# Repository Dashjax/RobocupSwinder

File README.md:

# RobocupSwinder
Robocup intro project with the goal to create a solenoid coil winder. :)

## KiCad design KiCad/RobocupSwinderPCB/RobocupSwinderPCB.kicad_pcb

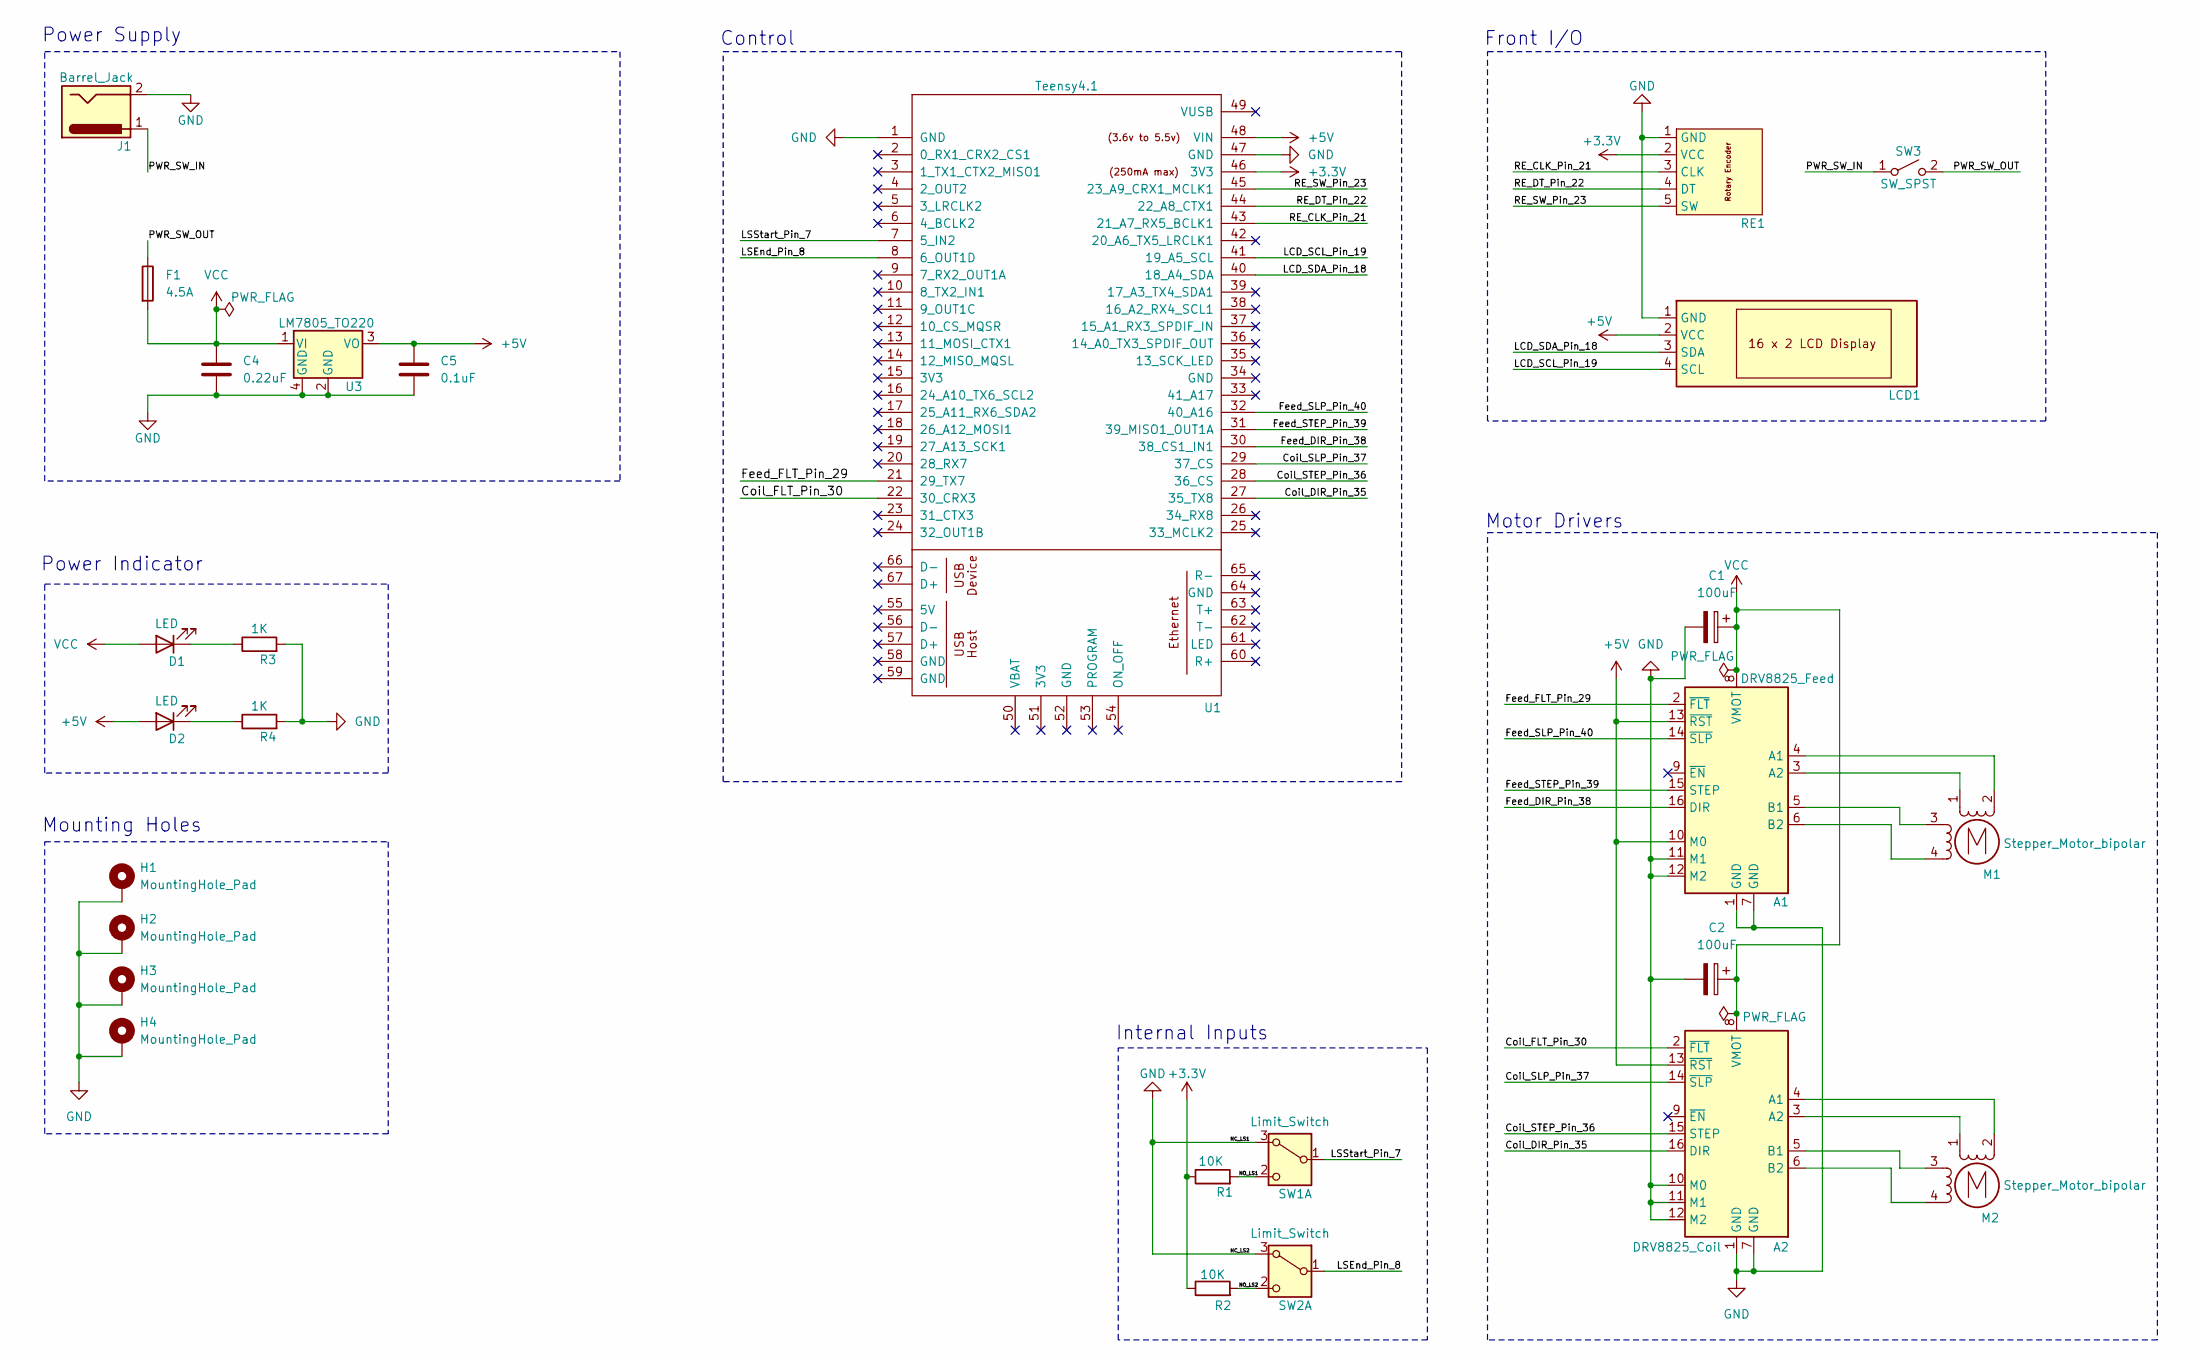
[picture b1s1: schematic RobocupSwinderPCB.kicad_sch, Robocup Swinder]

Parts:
A1: DRV8825_Feed; Pololu_Breakout-16_15.2x20.3mm
A2: DRV8825_Coil; Pololu_Breakout-16_15.2x20.3mm
C1, C2: 100uF; CP_Radial_D8.0mm_P3.50mm
C4: 0.22uF; C_1206_3216Metric_Pad1.33x1.80mm_HandSolder
C5: 0.1uF; C_1206_3216Metric_Pad1.33x1.80mm_HandSolder
D1, D2: LED; LED_0603_1608Metric_Pad1.05x0.95mm_HandSolder
F1: 4.5A; Fuse_1206_3216Metric
H1, H2, H3, H4: MountingHole_Pad; MountingHole_2.2mm_M2_DIN965_Pad
J1: Barrel_Jack; CUI_PJ-037A
LCD1: JST_XH_B4B-XH-A_1x04_P2.50mm_Vertical
M1, M2: Stepper_Motor_bipolar; JST_XH_B4B-XH-A_1x04_P2.50mm_Vertical
R1, R2: 10K; R_1206_3216Metric_Pad1.30x1.75mm_HandSolder
R3, R4: 1K; R_0603_1608Metric_Pad0.98x0.95mm_HandSolder
RE1: JST_XH_B5B-XH-A_1x05_P2.50mm_Vertical
SW1, SW2: Limit_Switch; JST_XH_B3B-XH-A_1x03_P2.50mm_Vertical
SW3: SW_SPST; JST_XH_B2B-XH-A_1x02_P2.50mm_Vertical
U1: Teensy4.1; Teensy41-Pins-Only_Silkscreen
U3: LM7805_TO220; SOT-223

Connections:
+3.3V: R1.1, R2.1, RE1.2 (VCC), U1.46 (3V3)
+5V: A1.10 (M0), A1.13 (~RST), A2.13 (~RST), C5.1, D2.2 (A), LCD1.2 (VCC), U1.48 (VIN), U3.3 (VO)
/Coil_DIR_Pin_35: A2.16 (DIR), U1.27 (35_TX8)
/Coil_FLT_Pin_30: A2.2 (~FLT), U1.22 (30_CRX3)
/Coil_SLP_Pin_37: A2.14 (~SLP), U1.29 (37_CS)
/Coil_STEP_Pin_36: A2.15 (STEP), U1.28 (36_CS)
/Feed_DIR_Pin_38: A1.16 (DIR), U1.30 (38_CS1_IN1)
/Feed_FLT_Pin_29: A1.2 (~FLT), U1.21 (29_TX7)
/Feed_SLP_Pin_40: A1.14 (~SLP), U1.32 (40_A16)
/Feed_STEP_Pin_39: A1.15 (STEP), U1.31 (39_MISO1_OUT1A)
/LCD_SCL_Pin_19: LCD1.4 (SCL), U1.41 (19_A5_SCL)
/LCD_SDA_Pin_18: LCD1.3 (SDA), U1.40 (18_A4_SDA)
/LSEnd_Pin_8: SW2.1 (C), U1.8 (6_OUT1D)
/LSStart_Pin_7: SW1.1 (C), U1.7 (5_IN2)
/NO_LS1: R1.2, SW1.2 (NO)
/NO_LS2: R2.2, SW2.2 (NO)
/PWR_SW_IN: J1.1, SW3.1 (A)
/PWR_SW_OUT: F1.1, SW3.2 (B)
/RE_CLK_Pin_21: RE1.3 (CLK), U1.43 (21_A7_RX5_BCLK1)
/RE_DT_Pin_22: RE1.4 (DT), U1.44 (22_A8_CTX1)
/RE_SW_Pin_23: RE1.5 (SW), U1.45 (23_A9_CRX1_MCLK1)
GND: A1.1 (GND), A1.7 (GND), A1.11 (M1), A1.12 (M2), A2.1 (GND), A2.7 (GND), A2.10 (M0), A2.11 (M1), A2.12 (M2), C1.2, C2.2, C4.2, C5.2, H1.1, H2.1, H3.1, H4.1, J1.2, LCD1.1 (GND), R3.2, R4.2, RE1.1 (GND), SW1.3 (NC), SW2.3 (NC), U1.1 (GND), U1.47 (GND), U3.2 (GND), U3.4 (GND)
unnamed: A1.4 (A1), M1.2 (-)
unnamed: A1.3 (A2), M1.1
unnamed: A1.5 (B1), M1.3
unnamed: A1.6 (B2), M1.4
unnamed: A2.4 (A1), M2.2 (-)
unnamed: A2.3 (A2), M2.1
unnamed: A2.5 (B1), M2.3
unnamed: A2.6 (B2), M2.4
unnamed: D1.1 (K), R3.1
unnamed: D2.1 (K), R4.1
VCC: A1.8 (VMOT), A2.8 (VMOT), C1.1, C2.1, C4.1, D1.2 (A), F1.2, U3.1 (VI)

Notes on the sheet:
Internal Inputs
Front I/O
Control
Power Supply
Motor Drivers
Mounting Holes
Power Indicator

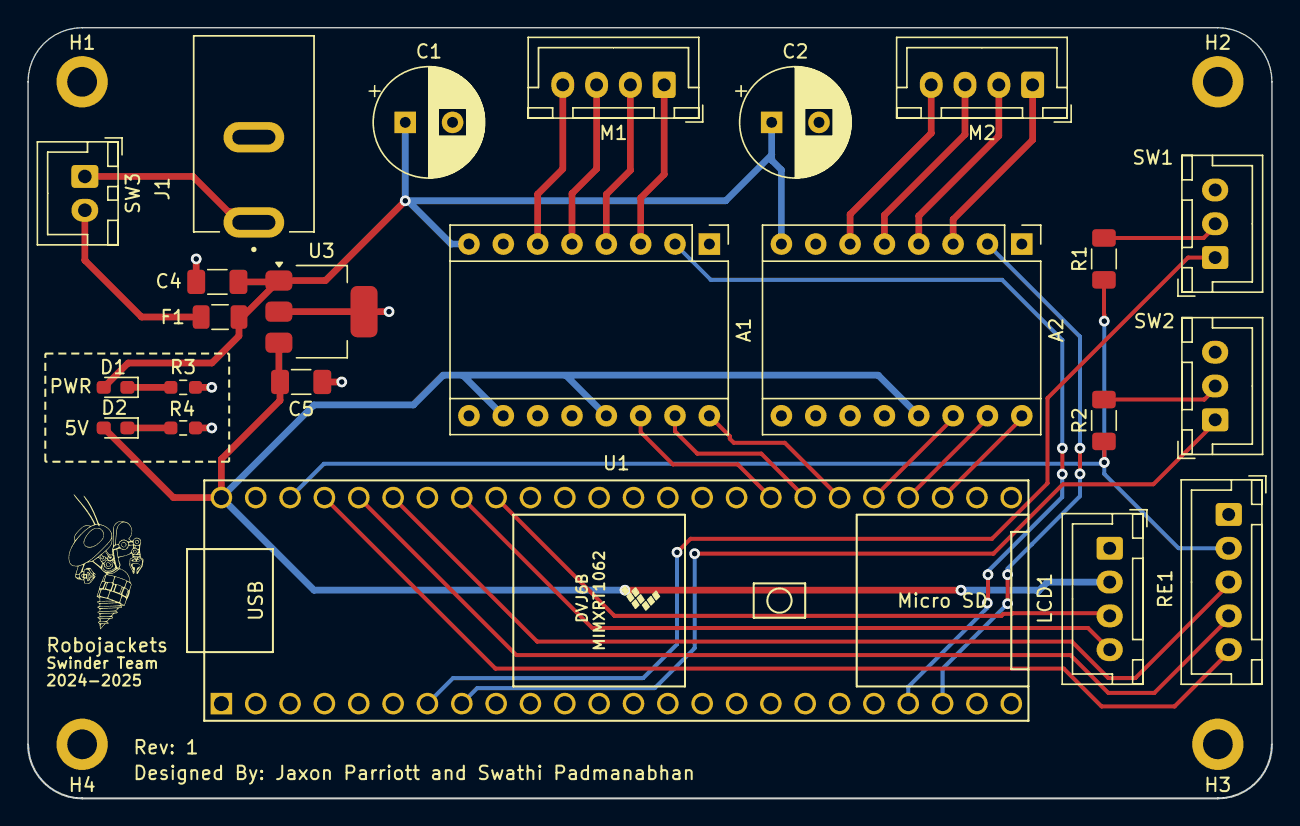
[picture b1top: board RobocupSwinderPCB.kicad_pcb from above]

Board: 2 copper layers, 92.0 x 57.0 mm, 27 parts (0 on the bottom side), 33 nets.

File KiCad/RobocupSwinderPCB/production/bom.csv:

Designator,Footprint,Quantity,Value,LCSC Part #
A1,Pololu_Breakout-16_15.2x20.3mm,1,DRV8825_Feed,
A2,Pololu_Breakout-16_15.2x20.3mm,1,DRV8825_Coil,
"C1, C2",CP_Radial_D8.0mm_P3.50mm,2,100uF,
C4,1206,1,0.22uF,
C5,1206,1,0.1uF,
"D1, D2",0603,2,LED,
F1,1206,1,4.5A,
J1,CUI_PJ-037A,1,Barrel_Jack,
LCD1,JST_XH_B4B-XH-A_1x04_P2.50mm_Vertical,1,~,
"M1, M2",JST_XH_B4B-XH-A_1x04_P2.50mm_Vertical,2,Stepper_Motor_bipolar,
"R1, R2",1206,2,10K,
"R3, R4",0603,2,1K,
RE1,JST_XH_B5B-XH-A_1x05_P2.50mm_Vertical,1,~,
"SW1, SW2",JST_XH_B3B-XH-A_1x03_P2.50mm_Vertical,2,Limit_Switch,
SW3,JST_XH_B2B-XH-A_1x02_P2.50mm_Vertical,1,SW_SPST,
U1,Teensy41-Pins-Only_Silkscreen,1,Teensy4.1,
U3,SOT-223,1,LM7805_TO220,

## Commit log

2025-01-27 Upload of initial files.
2025-01-27 Test upload
2025-01-27 Revert "Test upload"
    This reverts commit bc6afd239a551d7b86f59611108b2080e78a2b3a.
2025-01-27 Replaced position based code in preset select with direction based.
2025-01-27 Added documentation to value select.
2025-01-27 Added more documentaion to value select for input.
2025-01-27 Simplified rotary input for value selector.
2025-01-27 Added value format code from v3.0
2025-01-27 Added format_val support to val select
2025-01-27 Fixed screen clearing in val select
2025-01-27 Added link from val select to val editor
2025-01-27 Added confirmation screen to val select.
2025-01-27 Added framework for val editor
2025-01-27 Added left right movement to val editor
2025-01-27 Added done button to val editor.
2025-01-27 Working val editor
2025-01-27 Added documentation to value editor.
2025-01-27 Added confirm screen function.
2025-01-27 Minor adjustments to startup animation.
2025-01-27 Confirm screen screen setup.
2025-01-27 Added button function to confirm screen.
2025-01-27 Added encoder function to confirm screen.
2025-01-27 Added Documentation to confirm screen.
2025-01-27 Minor fixes.
2025-01-27 Added turns calculation function from v0.3
2025-01-27 Added stability delay to confirm screen.
2025-01-27 Added stability delay to val select.
2025-01-27 Added spin function.
2025-01-28 Added noBlink to exit of val editor.
2025-01-28 Fixed various formattings.
2025-01-28 Added safety check to format val length.
2025-01-28 Fixed formatting and delay issues with button input.
2025-01-28 Motor setup to spin.
2025-01-28 Added screen setup to spin.
2025-01-28 Added transition screen from zeroing to movement in spin.
2025-01-28 Added screen update to spin loop.
2025-01-28 Switched to a percent rather than step counter to decrease delay in process loop.
2025-01-28 Added presets to preset select.
2025-01-28 Re ordered val select to ensure visuals load.
2025-01-28 Switched from running all processes in the main loop to tying them directly to the previous function to allow entering at any point in the process.
2025-01-29 Remove temp val.
2025-01-29 Began setup for initial position.
2025-01-29 Added pause
2025-01-29 Added carriage initiation.
2025-01-29 A whole lotta stuff with motors.
2025-01-29 Same as last just with file actually saved.
2025-01-29 Fixed minor bugs.
2025-01-29 Added documentation to spin.
2025-02-03 Added 'Done' function with screen setup
2025-02-03 Added button press reading
2025-02-03 Added done function to spin
2025-02-03 Removed cursor and added button delay to done.
2025-02-03 Initial KiCad commit.
2025-02-03 helpful files
2025-02-03 full teensy footprint
2025-02-03 Fixed footprint library.
2025-02-12 Transition to arduino v0.5.
2025-02-12 Switched carriage motor to half step.
2025-02-12 Added motor fault detection.
2025-02-17 Added Rust starter files.
2025-02-17 Trimmed main file to barebones.
2025-02-17 More file cleanup to base template.
2025-02-19 Switched all encoder reads to interrupt based library.
2025-02-19 Switched to I2C port display.
2025-02-24 Added additional update to oldPosition for non-moving cases and changed val_editor and val_select to only update screen on change to decrease lag.
2025-02-24 Added sleep control of motors.
2025-02-24 Outlined basics of schematic.
2025-02-26 Updated pin assignments.
2025-02-26 Updated pin assignments again.
2025-03-03 A whole lotta stuff.
2025-03-05 Added Teensy footprint with silkscreen
2025-03-05 Updated pcb layout.
2025-03-05 Added buzz silkscreen.
2025-03-10 Routing.
2025-03-10 Update and output files.
2025-03-10 Update bom.csv
    added links
2025-03-10 Delete KiCad/RobocupSwinderPCB/production/bom.csv
    bye bye bom
2025-03-11 cleanup commit.
2025-03-11 Pcb cleanup
2025-03-12 More pcb cleanup.
2025-03-12 Removed filter inductor and cap.
2025-03-12 updated pin assignments in arduino code.
2025-03-25 fixed pin name.
2025-03-26 Redo bom.
2025-03-26 Lotta stuff.
2025-03-27 Fixed bom
2025-03-27 Rename final_bom.csv to old_final_bom.csv
2025-03-30 Add const values to lib.rs
2025-03-30 Add pin assignments and library imports to peripherals.rs
2025-03-30 Add rotary encoder library to Cargo.toml
2025-03-30 Update main.rs
    Added shared variables and initialized lcd, encoder, and stepper motor.
2025-10-14 Final commit till v1.0
2025-10-14 Added pio project for v1.0
2025-10-15 Started porting over code from v0.5
2025-10-17 Started framwork of library to hold all solenoid values and math.
2025-10-17 Added wire gauges to enum.
2025-10-17 Added turnsPerPass
2025-10-17 Started string formatting functions for Solenoid.
2025-10-17 Switch string formatting over to solenoid lib
2025-10-17 Switched task to enum format.
2025-10-17 Added wire gauge setters/getters
2025-10-17 Added remaining gauge edit functions.
2025-10-17 Started phasing out old solenoid implimentation
2025-10-20 Moved string formatting out of Solenoid lib to simplify and avoid overreach
2025-10-20 Added value editor to val select.
2025-10-20 Added confirm screen
2025-10-20 Added motor fault functionality.
2025-10-20 Finished fault and started pause.
2025-10-21 Added remaining functions, just need to finish doing math and testing.
2025-10-21 Added simple test for math and formatting.
2025-10-22 Near final stage.
2025-10-26 Switched return after end to valselect for easier re-run
2025-10-26 Remove old KiCad files.
2025-10-26 Added documentation.
2025-11-10 Test Commit
